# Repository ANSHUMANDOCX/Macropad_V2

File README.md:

## MACROPAD

This is a 20-key macropad with 2 rotary encoders, 2 analog slide potentiometers, and a 0.91" OLED display.

---

## List of Components

- Pro Micro RP2040  
- SSD1306 0.91" OLED  
- 20 MX-style keys  
- 2 Encoders  
- 2 PTA0643 Slide Potentiometers  
- WS2812B 2020 RGB LEDs  

---

## Plan

I wanted to make a macropad with enough keys for my purpose. I started out by getting a microcontroller with enough pins and one that is able to run CircuitPython, since I wanted to use KMK as the firmware. This can be programmed for MIDI control as well.  
It also has RGB LEDs for underglow.

The OLED screen will be attached via the QWIIC connector onboard.

---

## PCB and Case

## BOM 
### 📦 Component Cost Table

| Item                             | Supplier         | Price (USD) |
|----------------------------------|------------------|-------------|
| Screw & bolt                     | LCSC             | 0.34        |
| Rotary Encoder (DIP-5)           | LCSC             | 3.01        |
| PTA6043 Potentiometer (10kΩ)     | LCSC             | 3.37        |
| 1N4148 Diode                     | LCSC             | 0.84        |
|WS2812B 2020 RGB led              | LCSC             | 1.67        |
|SSD1306 0.91" OLED Display       | LCSC             | 2.01        |
| SL2.1A                          | LCSC             |1.22 |
| USB A Female                    | LCSC             |0.74 |
| Shipping (LCSC)                  | LCSC              |  3.73       |
| RP2040 Pro Micro + Qwiic        | Electronics Comp | 19.43       |
| Keycaps and Keys                | Stackskb         | 15.88       |
| PCB                              | JLCPCB           | 9.00        |
| Shipping                          | JLCPCB           | 14.00       |
| **Total**                        |                  | **$75.24**   |

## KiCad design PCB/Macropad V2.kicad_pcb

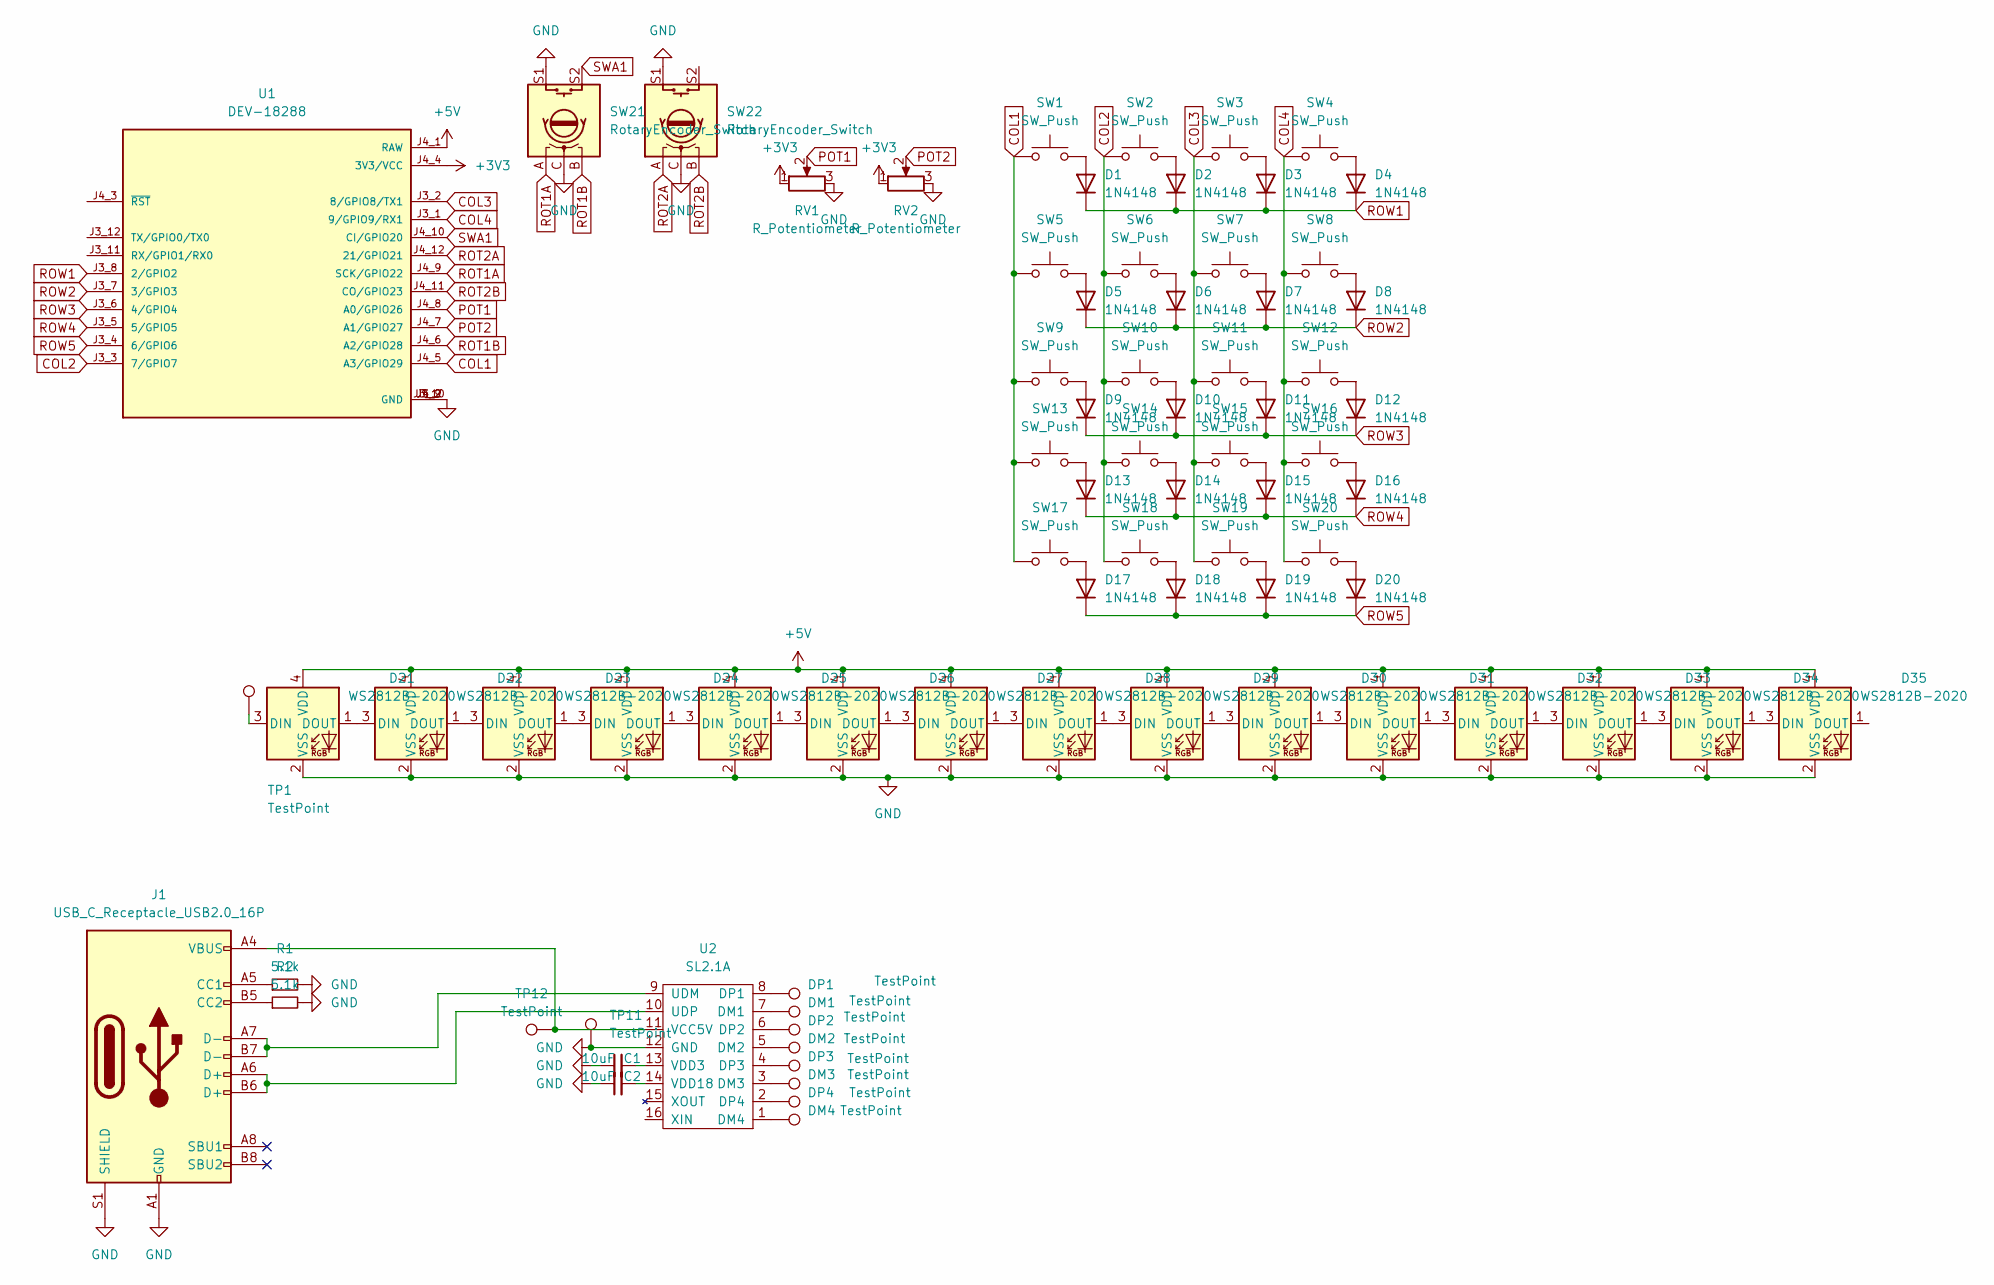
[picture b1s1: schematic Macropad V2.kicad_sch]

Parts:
C1, C2: 10uF; C_0805_2012Metric
D1, D2, D3, D4, D5, D6, D7, D8, D9, D10, D11, D12, D13, D14, D15, D16, D17, D18, D19, D20: 1N4148; D_DO-35_SOD27_P7.62mm_Horizontal
D21, D22, D23, D24, D25, D26, D27, D28, D29, D30, D31, D32, D33, D34, D35: WS2812B-2020; LED_WS2812B-2020_PLCC4_2.0x2.0mm
DM1, DM2, DM3, DM4: TestPoint; TestPoint_Pad_D1.5mm
DP1, DP2, DP3, DP4: TestPoint; TestPoint_Pad_D1.5mm
J1: USB_C_Receptacle_USB2.0_16P; USB_C_Receptacle_GCT_USB4105-xx-A_16P_TopMnt_Horizontal
R1, R2: 5.1k; R_0603_1608Metric
RV1, RV2: R_Potentiometer; Potentiometer_Bourns_PTA6043_Single_Slide
SW1, SW2, SW3, SW4, SW5, SW6, SW7, SW8, SW9, SW10, SW11, SW12, SW13, SW14, SW15, SW16, SW17, SW18, SW19, SW20: SW_Push; CHERRY
SW21, SW22: RotaryEncoder_Switch; RotaryEncoder_Alps_EC11E-Switch_Vertical_H20mm_CircularMoun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
TP1: TestPoint; TestPoint_Pad_D1.0mm
TP11, TP12: TestPoint; TestPoint_Pad_D1.5mm
U1: DEV-18288; MODULE_DEV-18288; PARTREV v11
U2: SL2.1A; SOIC-16_4.55x10.3mm_P1.27mm

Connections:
+3V3: RV1.1, RV2.1, U1.J4_4 (3V3/VCC)
+5V: D21.4 (VDD), D22.4 (VDD), D23.4 (VDD), D24.4 (VDD), D25.4 (VDD), D26.4 (VDD), D27.4 (VDD), D28.4 (VDD), D29.4 (VDD), D30.4 (VDD), D31.4 (VDD), D32.4 (VDD), D33.4 (VDD), D34.4 (VDD), D35.4 (VDD), U1.J4_1 (RAW)
COL1: SW1.1, SW5.1, SW9.1, SW13.1, SW17.1, U1.J4_5 (A3/GPIO29)
COL2: SW2.1, SW6.1, SW10.1, SW14.1, SW18.1, U1.J3_3 (7/GPIO7)
COL3: SW3.1, SW7.1, SW11.1, SW15.1, SW19.1, U1.J3_2 (8/GPIO8/TX1)
COL4: SW4.1, SW8.1, SW12.1, SW16.1, SW20.1, U1.J3_1 (9/GPIO9/RX1)
GND: C1.1, C2.1, D21.2 (VSS), D22.2 (VSS), D23.2 (VSS), D24.2 (VSS), D25.2 (VSS), D26.2 (VSS), D27.2 (VSS), D28.2 (VSS), D29.2 (VSS), D30.2 (VSS), D31.2 (VSS), D32.2 (VSS), D33.2 (VSS), D34.2 (VSS), D35.2 (VSS), J1.A1 (GND), J1.A12 (GND), J1.B1 (GND), J1.B12 (GND), J1.S1 (SHIELD), R1.2, R2.2, RV1.3, RV2.3, SW21.C, SW21.S1, SW22.C, SW22.S1, TP11.1, U1.J3_9 (GND), U1.J3_10 (GND), U1.J4_2 (GND), U2.12 (GND)
unnamed: D1.2 (A), SW1.2
unnamed: D2.2 (A), SW2.2
unnamed: D3.2 (A), SW3.2
unnamed: D4.2 (A), SW4.2
unnamed: D5.2 (A), SW5.2
unnamed: D6.2 (A), SW6.2
unnamed: D7.2 (A), SW7.2
unnamed: D8.2 (A), SW8.2
unnamed: D9.2 (A), SW9.2
unnamed: D10.2 (A), SW10.2
unnamed: D11.2 (A), SW11.2
unnamed: D12.2 (A), SW12.2
unnamed: D13.2 (A), SW13.2
unnamed: D14.2 (A), SW14.2
unnamed: D15.2 (A), SW15.2
unnamed: D16.2 (A), SW16.2
unnamed: D17.2 (A), SW17.2
unnamed: D18.2 (A), SW18.2
unnamed: D19.2 (A), SW19.2
unnamed: D20.2 (A), SW20.2
unnamed: D21.3 (DIN), TP1.1
unnamed: D21.1 (DOUT), D22.3 (DIN)
unnamed: D22.1 (DOUT), D23.3 (DIN)
unnamed: D23.1 (DOUT), D24.3 (DIN)
unnamed: D24.1 (DOUT), D25.3 (DIN)
unnamed: D25.1 (DOUT), D26.3 (DIN)
unnamed: D26.1 (DOUT), D27.3 (DIN)
unnamed: D27.1 (DOUT), D28.3 (DIN)
unnamed: D28.1 (DOUT), D29.3 (DIN)
unnamed: D29.1 (DOUT), D30.3 (DIN)
unnamed: D30.1 (DOUT), D31.3 (DIN)
unnamed: D31.1 (DOUT), D32.3 (DIN)
unnamed: D32.1 (DOUT), D33.3 (DIN)
unnamed: D33.1 (DOUT), D34.3 (DIN)
unnamed: D34.1 (DOUT), D35.3 (DIN)
unnamed: J1.A5 (CC1), R1.1
unnamed: J1.B5 (CC2), R2.1
unnamed: DM1.1, U2.7 (DM1)
unnamed: DM2.1, U2.5 (DM2)
unnamed: DM3.1, U2.3 (DM3)
unnamed: DM4.1, U2.1 (DM4)
unnamed: DP1.1, U2.8 (DP1)
unnamed: DP2.1, U2.6 (DP2)
unnamed: DP3.1, U2.4 (DP3)
unnamed: DP4.1, U2.2 (DP4)
unnamed: J1.A7 (D-), J1.B7 (D-), U2.9 (UDM)
unnamed: J1.A6 (D+), J1.B6 (D+), U2.10 (UDP)
unnamed: J1.A4 (VBUS), J1.A9 (VBUS), J1.B4 (VBUS), J1.B9 (VBUS), TP12.1, U2.11 (VCC5V)
unnamed: C1.2, U2.13 (VDD3)
unnamed: C2.2, U2.14 (VDD18)
POT1: RV1.2, U1.J4_8 (A0/GPIO26)
POT2: RV2.2, U1.J4_7 (A1/GPIO27)
ROT1A: SW21.A, U1.J4_9 (SCK/GPIO22)
ROT1B: SW21.B, U1.J4_6 (A2/GPIO28)
ROT2A: SW22.A, U1.J4_12 (21/GPIO21)
ROT2B: SW22.B, U1.J4_11 (CO/GPIO23)
ROW1: D1.1 (K), D2.1 (K), D3.1 (K), D4.1 (K), U1.J3_8 (2/GPIO2)
ROW2: D5.1 (K), D6.1 (K), D7.1 (K), D8.1 (K), U1.J3_7 (3/GPIO3)
ROW3: D9.1 (K), D10.1 (K), D11.1 (K), D12.1 (K), U1.J3_6 (4/GPIO4)
ROW4: D13.1 (K), D14.1 (K), D15.1 (K), D16.1 (K), U1.J3_5 (5/GPIO5)
ROW5: D17.1 (K), D18.1 (K), D19.1 (K), D20.1 (K), U1.J3_4 (6/GPIO6)
SWA1: SW21.S2, U1.J4_10 (CI/GPIO20)

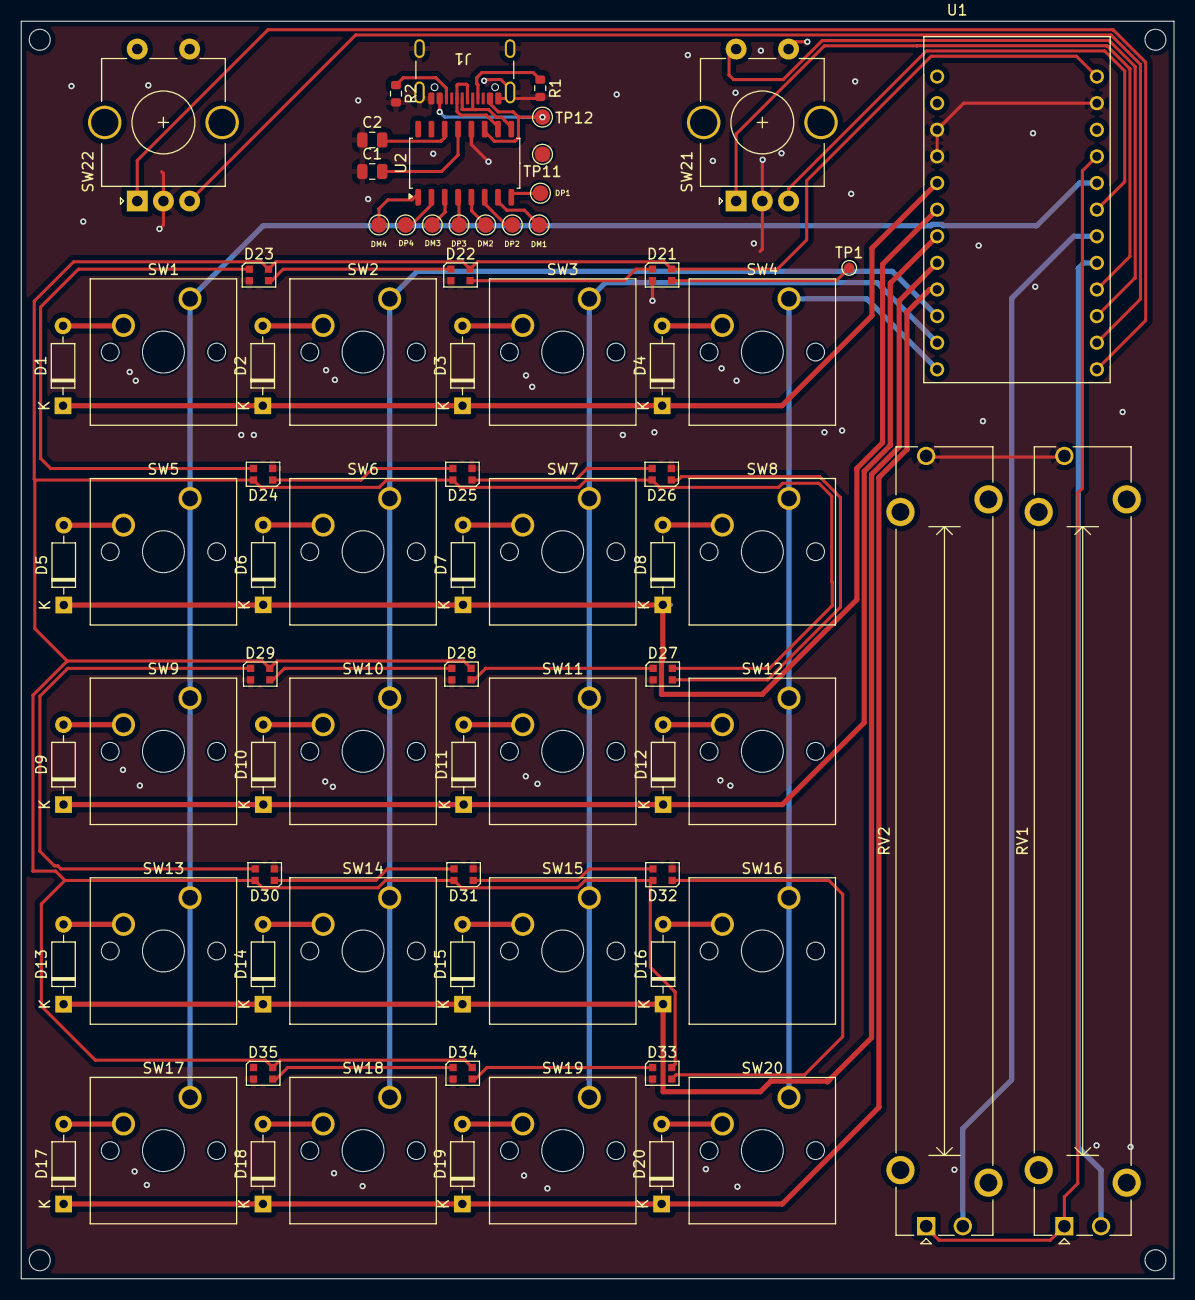
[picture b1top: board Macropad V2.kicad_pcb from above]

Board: 2 copper layers, 110.0 x 120.0 mm, 77 parts (0 on the bottom side), 69 nets.

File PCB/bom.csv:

Designator,Footprint,Quantity,Value,LCSC Part #
"C1, C2",0805,2,10uF,
"D1, D10, D11, D12, D13, D14, D15, D16, D17, D18, D19, D2, D20, D3, D4, D5, D6, D7, D8, D9",D_DO-35_SOD27_P7.62mm_Horizontal,20,1N4148,
"D21, D22, D23, D24, D25, D26, D27, D28, D29, D30, D31, D32, D33, D34, D35",LED_WS2812B-2020_PLCC4_2.0x2.0mm,15,WS2812B-2020,
"DM1, DM2, DM3, DM4, DP1, DP2, DP3, DP4, TP11, TP12",TestPoint_Pad_D1.5mm,10,TestPoint,
J1,USB_C_Receptacle_GCT_USB4105-xx-A_16P_TopMnt_Horizontal,1,USB_C_Receptacle_USB2.0_16P,
"R1, R2",0603,2,5.1k,
"RV1, RV2",Potentiometer_Bourns_PTA6043_Single_Slide,2,R_Potentiometer,
"SW1, SW10, SW11, SW12, SW13, SW14, SW15, SW16, SW17, SW18, SW19, SW2, SW20, SW3, SW4, SW5, SW6, SW7, SW8, SW9",CHERRY,20,SW_Push,
"SW21, SW22",RotaryEncoder_Alps_EC11E-Switch_Vertical_H20mm_CircularMountingHoles,2,RotaryEncoder_Switch,
TP1,TestPoint_Pad_D1.0mm,1,TestPoint,
U1,MODULE_DEV-18288,1,DEV-18288,
U2,SOIC-16_4.55x10.3mm_P1.27mm,1,SL2.1A,
